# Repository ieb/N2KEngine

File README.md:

# N2K Engine Monitor

This monitors an engine, mostly temperatures and fuel, emitting suitable N2K messages. Targeting a Volvo Penta D2-40. Code and pcb are based on the interface board in https://github.com/ieb/EngineManagement, however this time the pcb is from scratch using a Atmel 328p directly to make the unit more robust. The original has been in service for 3 years with no problems seen, outlasting the Volvo Penta MDI unit, which failed 2x in < 4 years. Ok, the replacement was based on relays following the Perkins schematic for the same engine, so not really hard to do.

# PCB

Single board. If using a 328p chip you will need to flash the bootloader. See programBootLoader for details. 

## 328p based board 

<div>

</div>

## Attiny3226 Board, 12bit ADCs and better RPM accuracy

<div>

</div>

# Setup

Setup starting with a new board, this is for 3226 which the preferred board.

* Test the board supply to check power consumption, should be about 30mA at both 5v and 12v.
* Connect up a UDPI programmer, and serial monitor.
* Burn Fuses, and tune the internal clock on the 3226, see tuning3226/README.md
* Upload the code.
* Connect a CAN bus with 1 other device.
* Verify CAN messages are sent and received (menu item d)
* Measure and set the supply voltage to the chip after powering with 12v. (menu item V)
* Check the Sensor diagnostics (menu item D, and M), might need to connect some NTC sensors and fake up flywheel source.
* Set the engine hours to match the existing board.
* Install the board

## Connection notes

* The GND connection must be made to the engine block (star pattern) to avoid GND voltage differences when the anternator is charging. Do not GND on the battery as that will result in dips in the coolant temperature of 5C or more. The battery voltage will include the GND drop on the charging line.

* The exhaust NCT should be connected to a part of the wet exhaust with good thermal connection to the inside of the exhaust. Do not connect to the elbow on the engine as this could result in false alarms when starting a warm engine. The trigger level is 45C or an 8C every 30s rise. Typically an exaust in UK waters on a D2-40 rests at 34-37C and rises rapidly should raw water fail.

## Changes from original build 4 years ago

* All components SMD, no draughtboards or modules with pin headers to fail.
* Switched from a LM385 to a LMV393 for the flywheel pulse generator as all I need is a clean square wave to count the pulses. (actually I miss ordered 10 LMV393's and then switched over).
* Changed to a 16MHz crystal on the MCP2515 since this is what the 328p is using. Perhaps 1 crystal would work for both, but probably not.

# Memory usage

after reducing memory requirements (580 used before), varies up an down a bit with debug.

attiny3226

    RAM:   [==        ]  20.1% (used 619 bytes from 3072 bytes)
    Flash: [========  ]  81.1% (used 26579 bytes from 32768 bytes)
NB, no malloc in use in code.
Over 77% Flash usag pio inspect no longer works, however removing One wire code may give enough space for debug symbols to allow inspect to work

# Status bits.

The status bits in PGN 127489 are set to indicate an alarm condition.

Alarm set levels and alarm clear levels are in enginesensors.h

WHen an alarm condition is set if the check engine, maintenance or emergency stop bits are set, they are not
cleared when the alarm clears. Generally advisable to stop the engine and check.

Emergency stop will be set when temperatures are too high. Best to stop the engine before damage occurs.

Over Temperature status 1 bit 1 set when over temperature is suspected including coolant (> 97C), exhaust > 45C, alternator > 110C, engine room > 70C. Will also set check engine and engine emergency shutdown alarms.

Low oil pressure alarm is set when oil pressure is < 10psi.

If sensors fail then engine comms alarm is set.

Water flow alarm uses the wet exhaust silencer probe as a proxy for raw water flow. The probe is mounted on the silencer body, which is in direct contact with the wet exhaust but thermally isolated from the engine block and heat exchanger — so silencer temperature reflects exhaust gas vs raw water flow only, and is not biased by block temperature on a warm restart. Two independent triggers, both gated on engine running, past the start-up grace period, and not stopping:

* Absolute over-temp: exhaust > 45C. WATER_FLOW and CHECK_ENGINE are set on the first sample; EMERGENCY_STOP is held off until the condition has persisted for 5s so a single noisy ADC sample cannot trip it.
* Rate-of-rise: exhaust climbs more than 8C in any 30s window once past the 35C baseline. This catches a flow failure before the absolute threshold (the 21-Jun-2026 incident showed a +9C rise in the first 30s while still well below 45C).

A coolant-vs-exhaust convergence check was previously included but removed: on a warm restart the silencer takes several minutes to thermalize while coolant is already at operating temperature, producing a coolant–exhaust gap that approaches the trip margin under entirely healthy conditions.

The alarm clears only once exhaust drops below 38C (widened from 40C) to avoid chatter on a cooling elbow.

Charge indicator alarm is set when the alternator voltage is < 12.8V

Engine shutdown alarm will be set when the engine is shutting down.

Other alarms are not set at this time.

# Building and Uploading

## Attiny3226 based board

Use UDPI. I use the old, slow and slightly buggy jtag2udpi programmer loaded onto an Uno. I use https://github.com/ieb/jtag2updi forked just in case. After programming the Uno needs a 10uF cap between reset and ground to prevent a reset on the Uno when programming starts.  The UDPI output is on Digital Pin 6 and connects via a 4K7 Resistor to the UDPI pin on the Attiny3226. The target board should be powered separately, and the serial monitor can remain attached while programming. Do not power the board using both a serial converter and the 12v power supply as this will cause the serial port to draw too much USB current and be shutdown. Programing setup is in platformio.ini. Before programming a fresh chip, set the fuses to set the CPU Frequency.

Fresh boards also need to go through a runing process , see tuning3226/

Obviously edit platform.ini with the correct serial ports for upload and monitoring.

    pio run -e attiny3226 -t fuses

Then upload code with an upload command. Fuses only need to be set once per chip.

    pio run -e attiny3226 -t upload

To monitor 

    pio device monitor

### Clock Tuning 3226

The 3226 board uses an internal oscilator due to lack of pins and so it needs tuning from a board with a quartz crystal as per https://github.com/SpenceKonde/megaTinyCore/blob/master/megaavr/extras/Ref_Tuning.md. The Tuning source needs to be https://github.com/SpenceKonde/megaTinyCore/tree/master/megaavr/libraries/megaTinyCore/examples/TuningSource uploaded onto a Uno or any 328p with pin 9 available. The UNO must have an real crystal not a resonator.  The tuning code is https://github.com/SpenceKonde/megaTinyCore/tree/master/megaavr/libraries/megaTinyCore/examples/megaTinyTuner, but for these boards must be modified to use PB1 as the timing pin since this is exposed directly. (Oil pressure sense).  Copies of both of these are in tuning as they needed minor modifications.

## 328p based board

Can be built on any 328p suitably wired, however to build using the pcb design first flash a bootloader, see [programBootLoader/README.md] for details, then come back here.

Having flashed with the urbootloader connect a serial adapter configured for 5V to the serial header pins, adjust platform.ini to reflect the serial port and run

    pio run -t upload

to monitor

    pio device monitor

Do not attempt to power the board both on the 12v line and through the serial port 5v at the same time. This will probably shutdown the USB port on your laptop (or worse produce some smoke) Monitoring over serial can be done provided only GND, TX and RX are attached. Ie no power from the serial adapter.

# LM393 RPM to pulses

Critical that this chip as a 100nF decoupling capacitor. Without it it will generate pulses from power supply noise with the inputs shorted together. See schematic. LTSpice models don't predict this behavior.

# Engine Events

Stores upto 29 events in EEPROM, with a 15s resolution and one of upto 255 types.
All the following PGNS have standard priorietary PGN format + a Function code byte.
The Manufactore code is 2046 and the Industry is Marine, ie 4.

# PGN Abuse

Since Raymarine instuments display only a asubset of PGNs, some are beeing abused to get critical temperatures avialable on the insturments.

* alternator temperature, critical for LiFePO4 charging, is sent as oil temperature in Dynamic Engine Parameters (PGN 127489)
* ehxhaust temperature, critical for raw water flow monitoring, is sent as transmission oil temperature in Dynamic Transmiossion Parameters (PGN 127493L)

# Temperature PGN 130312 non standard IDs

* Exhaust temperature is sent as ID 30
* Additional OneWire Temperature probes are sent as IDs 31-35 where present.

## PGN 65305L

Standard  Packet proprietary, 8 bytes

| Field | Length | Value     | Description            |
|-----------------------------------------------------|
| 1     | 11 bits| 2046      | Manufacturer code      |
| 2     | 2 bits |           | Rserved                |
| 3     | 3 bits | 4 (0b100) | Industry Code          |
| 4     | 8 bits |           | Requst Function Number |
| 5     | 5 bytes|           | reserved/payload       |

|  Function | Description         | Valid PGN | Response                              |
|-----------|---------------------|-----------|---------------------------------------|
| 11        | Get events          | 65305L    | Events PGN 130817L Functon 12         |
| 12        | Get events response | 130817L   | List of events                        |
| 13        | Clear events        | 65305L    | ACK PGN 65305L Functon 14, no payload |
| 14        | Clear events ACK    | 65305L    | Ack clear events, no payload          |

## PGN 130817L

| Field | Length | Value     | Description            |
|-------|--------|-----------|------------------------|
| 1     | 11 bits| 2046      | Manufacturer code      |
| 2     | 2 bits |           | Rserved                |
| 3     | 3 bits | 4 (0b100) | Industry Code          |
| 4     | 8 bits |           | Requst Function Number |

## Function 12

| Field   | Length  | Value               | Description                            | 
|---------|---------|---------------------|----------------------------------------|
| 4       | 1 byte  | uint8_t             | Number of events                       |
| 5+(n*4) | 1 byte  | uint8_t             | Event ID                               |
| 6+(n*4) | 3 bytes | 3Byte UDouble 0.001 | Engine Hours of event (15s resolution) |

| Event ID | Meaning |
|----------|---------|
| 0        | Current engine hours, no event |
| 1        | Engine Stop |
| 2        | Low Oil Pressure |
| 3        | High Coolant Temperature |
| 4        | High Exhaust Temperature |
| 5        | High Alternator Temperature |
| 6        | High Engine Room Temperature |

# Todo

* [x] build board.
* [x] Flash bootloader and test
* [x] Port code from original
* [x] Allow for 16MHz MCP2515 oscillator, current library uses 8MHz.
* [x] Handle when engine not running, now that device is powered from CanBus
* [x] Reduce memory requirements in EngineSensorts and bind measurements to messages.
* [x] PR SmallNMEA2000 with changes
* [x] Test and Calibrate NTCs
* [x] Test and Calibrate Coolant and fuel
* [x] Test On N2K Bus
* [x] Implement 1 wire
* [x] Allow Engine Hours to be set via serial
* [x] Improve status and diagnostics to include n2k traffic
* [x] Implement status alarms
* [x] Consider swapping NTC4 for a oil pressure sensor if it can be accommodated.
* [x] Power from Engine supply since oil pressure sensors use > 10mA typically. This means fuel levels and temperature will only be available with engine controls turned on.
* [x] Check voltage calibration, some doubt over digtal multi meter accuracy used previously - verified against a ADS1115 to be accurate
* [x] Add firmware version, shows on the help, press h when connected over serial.
* [x] Create a attiny3226 based board, with 12bit ADCs for better resolution on the voltages.
* [x] Calibrate CPU clock
* [x] Verify RPM accuracy (measured at +- 0.2% relative to calibrated 16Mhz crystal)
* [x] Verify NTC and other ADC readings.
* [x] Install onboard
* [x] Implement event storage
* [x] Implement PGN proprietary messages to query engine events.
* [x] Update schematic to improve ADC stability when charging main LiFePO4s
* [x] Fix OneWire on Attiny3226 (see lib/vportonewire)
* [x] Fix event streaming to contain the right number of events including current hours.
* [x] Read stop button, on PC0. This will go to 12V when the solenois is powered.
* [x] Lowered alternator low voltage alarm to 12.2v and added window for overheat to combat high noise levels on the coolant sensor.
* [x] Added window period for all alarms to avoid 1 reading triggering alarm condition, set a 5s. 
* [x] Fixed (hopefully, need to test on engine) noise in in Engine Coolant readings, due to 12v ripple.
* [ ] Check the divders, which we specked at 100K/47K which could be too large for the ADC capacitance.

# Could do... but probably will not

The board currently runs of switched engine power, so to read fuel tank and batteries the engine has to be turned on. This is good, since power consumption becomes irrelevant although its typically < 80mA. I could optimize so that the board could be powered from the Can bus, but probably wont. Better to have it off when 
not relevant.. eg when sailing.

# New Board check list

* Oil sensor with pot
* NTCs, set Vdd then 10K == 25C, 22K == 8C, Check thermstor against room temp and body temp.
* Check Fuel 190R == full 0R == empty, linear, 120R == 120/190 = 63%  47/190 == 24
* Check AltV by connecting to suppy V
* Check Coolant, Supply -> 1K top. 22R == 120C, 120R == 60+10*(134-120)/(134-97) = 63
* Check RPM with a 1KHz signal
* Check oneWire
* Check CAN and engine events are responding, verifies can read and write.

# Engine overheat data from 21 July 2026.

Had been motoring for about 45m, 2.2K rpm all stable.

* 10:08:45 Coolant 87C, Exhaust 38.4C, Engine Room 57. raw water hose detaches, sudden drop in Engine Room temperature due to water spraying engine bay. Exhaust note changed.
* 10:09:00 Coolant 90C, Exhaust 40.2, Engine 50C
* 10:09:15 Coolant 92.7C, Exhaust 47.1, Engine 49.4C
* 10:09:30 Coolant 95.2C, Exhaust 51.9, Engine 48.6C  <<< Should have alarmed here.
* 10:09:45 Coolant 97.4C, Exhaust 57.9, Engine 47.3C
* 10:09:55 Coolant 98.3C, Exhaust 62.6, Engine 47.1C  engine was turned off before overheat.

Exhaust elbow temperature rises rapidly 22C over 1m vs 8C over the same period for the engine coolant temperature, although at the time no raw water alarm sounded as the limit was set at 80C and there was no display showing exhaust temperature.

Exhaust elbow temperature seems to be a strong indicator of water flow once the engine is running at temperature.

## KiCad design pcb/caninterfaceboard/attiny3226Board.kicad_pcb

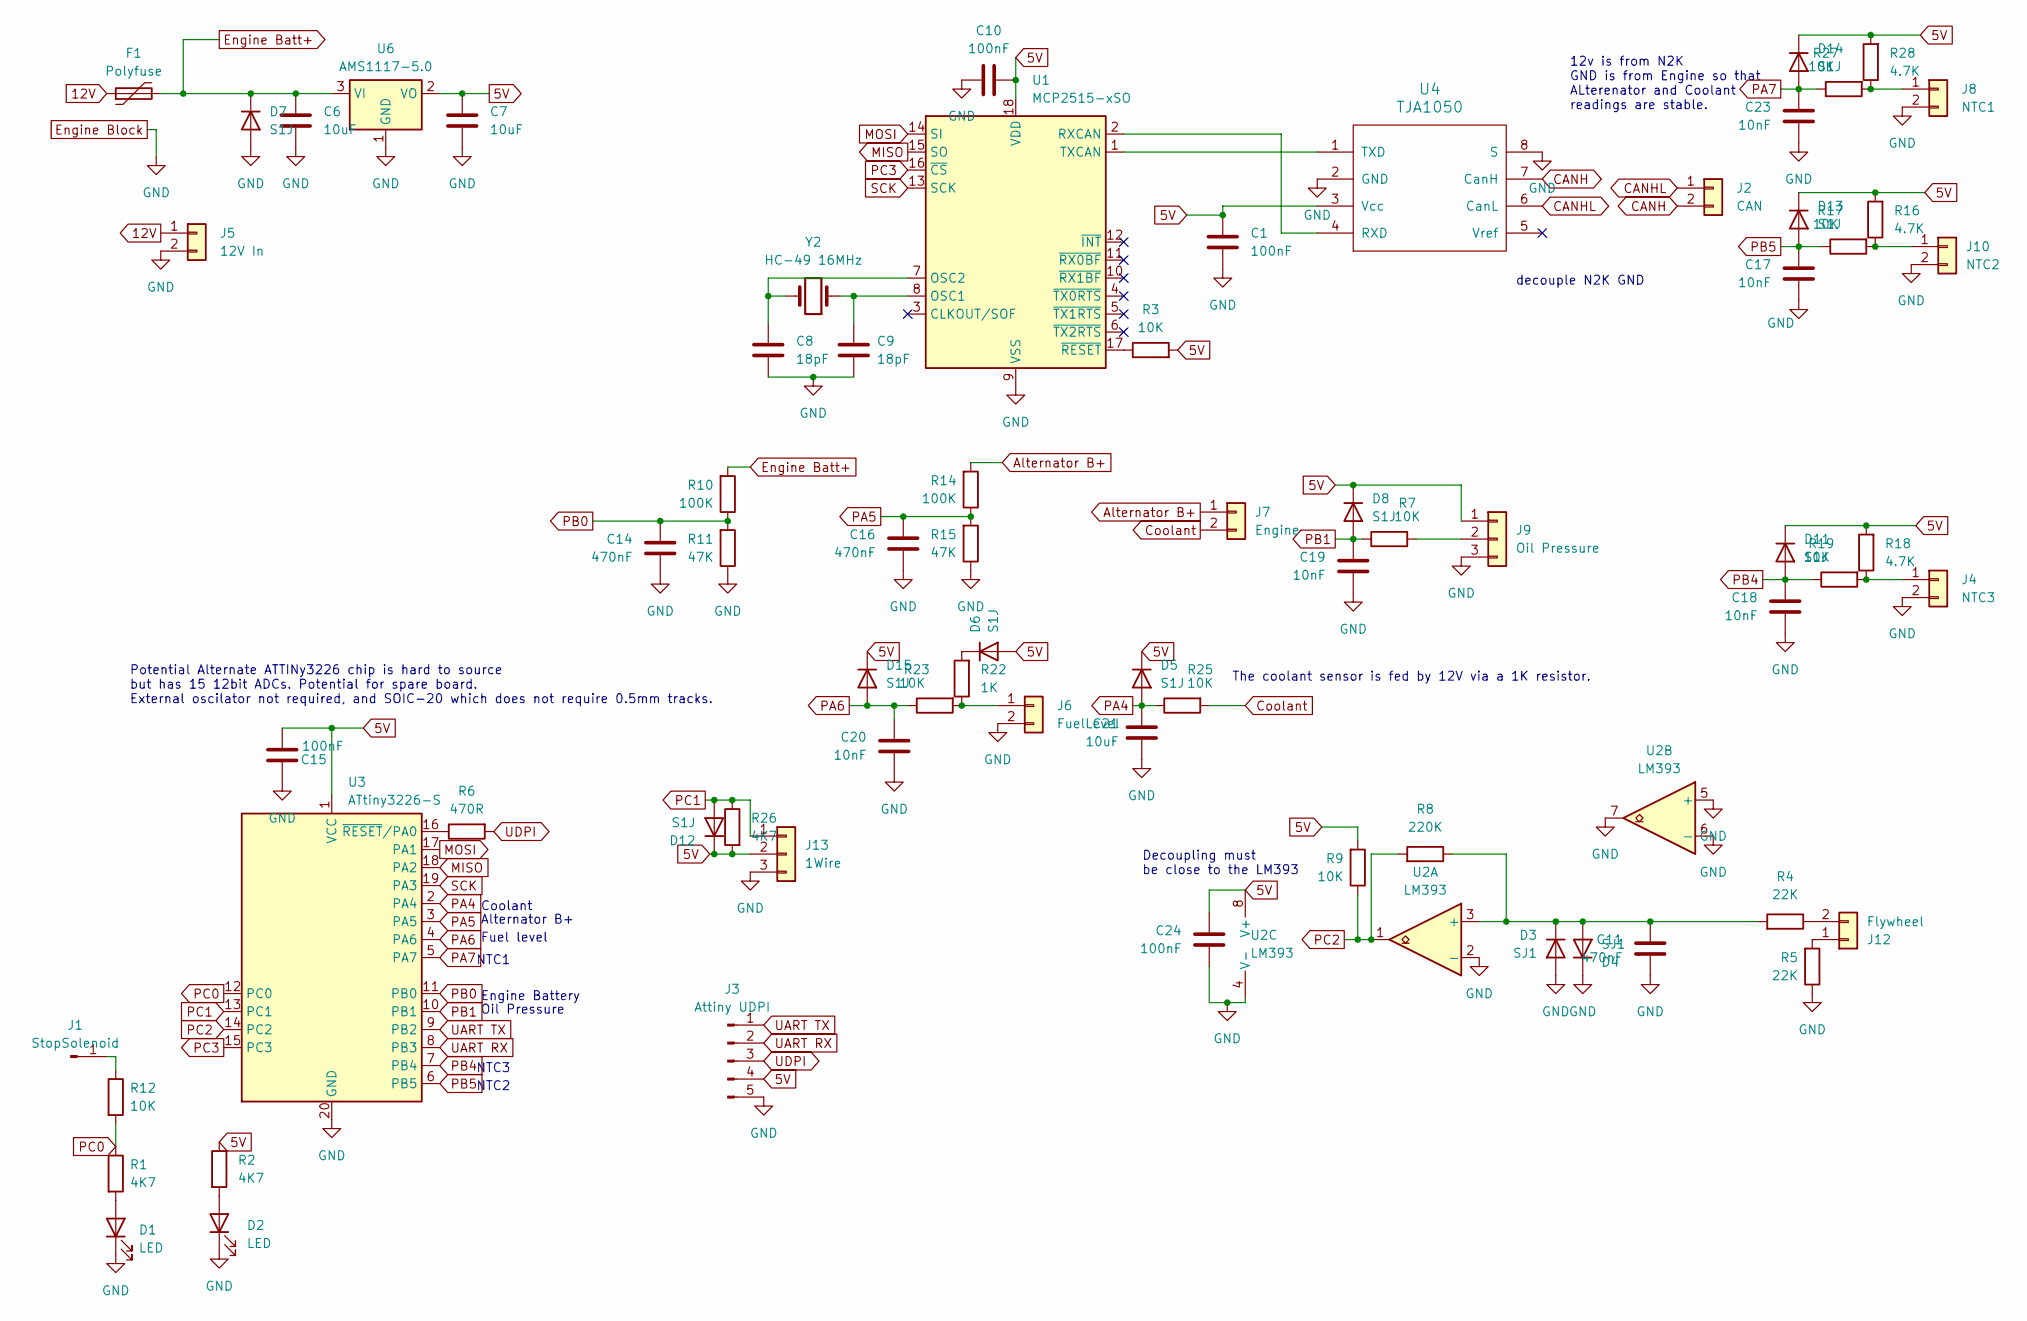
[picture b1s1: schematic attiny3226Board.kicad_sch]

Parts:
C1, C10, C15, C24: 100nF; C_0805_2012Metric_Pad1.18x1.45mm_HandSolder
C6, C7: 10uF; C_1206_3216Metric_Pad1.33x1.80mm_HandSolder
C8, C9: 18pF; C_0805_2012Metric_Pad1.18x1.45mm_HandSolder
C11, C14, C16: 470nF; C_0805_2012Metric_Pad1.18x1.45mm_HandSolder
C17, C18, C19, C20, C23: 10nF; C_0805_2012Metric_Pad1.18x1.45mm_HandSolder
C21: 10uF; C_0805_2012Metric_Pad1.18x1.45mm_HandSolder
D1, D2: LED; LED_0805_2012Metric_Pad1.15x1.40mm_HandSolder
D3, D4: SJ1; D_SOD-123
D5, D6, D7, D8, D11, D12, D13, D14, D15: S1J; D_0805_2012Metric_Pad1.15x1.40mm_HandSolder
F1: Polyfuse; Fuse_1812_4532Metric_Pad1.30x3.40mm_HandSolder
J1: StopSolenoid; PinSocket_1x01_P2.54mm_Vertical
J2: CAN; TerminalBlock_Phoenix_MKDS-1,5-2-5.08_1x02_P5.08mm_Horizont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
J3: Attiny UDPI; PinHeader_1x05_P2.54mm_Vertical
J4: NTC3; TerminalBlock_Phoenix_MKDS-1,5-2-5.08_1x02_P5.08mm_Horizont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
J5: 12V In; TerminalBlock_Phoenix_MKDS-1,5-2-5.08_1x02_P5.08mm_Horizont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
J6: FuelLevel; TerminalBlock_Phoenix_MKDS-1,5-2-5.08_1x02_P5.08mm_Horizont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
J7: Engine; TerminalBlock_Phoenix_MKDS-1,5-2-5.08_1x02_P5.08mm_Horizont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
J8: NTC1; TerminalBlock_Phoenix_MKDS-1,5-2-5.08_1x02_P5.08mm_Horizont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
J9: Oil Pressure; TerminalBlock_Phoenix_MKDS-1,5-3-5.08_1x03_P5.08mm_Horizont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
J10: NTC2; TerminalBlock_Phoenix_MKDS-1,5-2-5.08_1x02_P5.08mm_Horizont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
J12: Flywheel; TerminalBlock_Phoenix_MKDS-1,5-2-5.08_1x02_P5.08mm_Horizont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
J13: 1Wire; TerminalBlock_Phoenix_MKDS-1,5-3-5.08_1x03_P5.08mm_Horizont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
R1, R2, R26: 4K7; R_0805_2012Metric_Pad1.20x1.40mm_HandSolder
R3, R7, R9, R12, R17, R19, R23, R25, R27: 10K; R_0805_2012Metric_Pad1.20x1.40mm_HandSolder
R4, R5: 22K; R_0805_2012Metric_Pad1.20x1.40mm_HandSolder
R6: 470R; R_0805_2012Metric_Pad1.20x1.40mm_HandSolder
R8: 220K; R_0805_2012Metric_Pad1.20x1.40mm_HandSolder
R10, R14: 100K; R_0805_2012Metric_Pad1.20x1.40mm_HandSolder
R11, R15: 47K; R_0805_2012Metric_Pad1.20x1.40mm_HandSolder
R16, R18, R28: 4.7K; R_0805_2012Metric_Pad1.20x1.40mm_HandSolder
R22: 1K; R_0805_2012Metric_Pad1.20x1.40mm_HandSolder
U1: MCP2515-xSO; SOIC-18W_7.5x11.6mm_P1.27mm
U2: LM393; SOIC-8_3.9x4.9mm_P1.27mm
U3: ATtiny3226-S; SOIC-20W_7.5x12.8mm_P1.27mm
U4: TJA1050; SOIC-8_3.9x4.9mm_P1.27mm
U6: AMS1117-5.0; SOT-223-3_TabPin2
Y2: HC-49 16MHz; Crystal_SMD_HC49-SD

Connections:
5V: C1.1, C7.1, C10.2, C15.2, C24.2, D5.1 (K), D6.2 (A), D8.1 (K), D11.1 (K), D12.1 (K), D13.1 (K), D14.1 (K), D15.1 (K), J3.4, J9.1, J13.2, R2.1, R3.2, R9.2, R16.2, R18.2, R26.2, R28.2, U1.18 (VDD), U2.8 (V+), U3.1 (VCC), U4.3 (Vcc), U6.2 (VO)
12V: F1.1, J5.1
Alternator B+: J7.1, R14.2
CANH: J2.2, U4.7 (CanH)
CANHL: J2.1, U4.6 (CanL)
Coolant: J7.2, R25.2
Engine Batt+: C6.1, D7.1 (K), F1.2, R10.2, U6.3 (VI)
Engine Block: C1.2, C6.2, C7.2, C8.1, C9.1, C10.1, C11.1, C14.1, C15.1, C16.1, C17.1, C18.1, C19.1, C20.1, C21.1, C23.1, C24.1, D1.1 (K), D2.1 (K), D3.2 (A), D4.1 (K), D7.2 (A), J3.5, J4.2, J5.2, J6.2, J8.2, J9.3, J10.2, J13.3, R5.1, R11.1, R15.1, U1.9 (VSS), U2.2 (-), U2.4 (V-), U2.5 (+), U2.6 (-), U2.7, U3.20 (GND), U4.2 (GND), U4.8 (S), U6.1 (GND)
MISO: U1.15 (SO), U3.18 (PA2)
MOSI: U1.14 (SI), U3.17 (PA1)
unnamed: D1.2 (A), R1.2
unnamed: D2.2 (A), R2.2
unnamed: C11.2, D3.1 (K), D4.2 (A), R4.2, R8.1, U2.3 (+)
unnamed: D6.1 (K), R22.2
unnamed: J1.1, R12.1
unnamed: J4.1, R18.1, R19.2
unnamed: J6.1, R22.1, R23.2
unnamed: J8.1, R27.2, R28.1
unnamed: J9.2, R7.2
unnamed: J10.1, R16.1, R17.2
unnamed: J12.1, R5.2
unnamed: J12.2, R4.1
unnamed: C9.2, U1.8 (OSC1), Y2.1
unnamed: C8.2, U1.7 (OSC2), Y2.2
unnamed: U1.2 (RXCAN), U4.4 (RXD)
unnamed: U1.1 (TXCAN), U4.1 (TXD)
unnamed: R3.1, U1.17 (~RESET)
unnamed: R6.1, U3.16 (~RESET/PA0)
PA4: C21.2, D5.2 (A), R25.1, U3.2 (PA4)
PA5: C16.2, R14.1, R15.2, U3.3 (PA5)
PA6: C20.2, D15.2 (A), R23.1, U3.4 (PA6)
PA7: C23.2, D14.2 (A), R27.1, U3.5 (PA7)
PB0: C14.2, R10.1, R11.2, U3.11 (PB0)
PB1: C19.2, D8.2 (A), R7.1, U3.10 (PB1)
PB4: C18.2, D11.2 (A), R19.1, U3.7 (PB4)
PB5: C17.2, D13.2 (A), R17.1, U3.6 (PB5)
PC0: R1.1, R12.2, U3.12 (PC0)
PC1: D12.2 (A), J13.1, R26.1, U3.13 (PC1)
PC2: R8.2, R9.1, U2.1, U3.14 (PC2)
PC3: U1.16 (~CS), U3.15 (PC3)
SCK: U1.13 (SCK), U3.19 (PA3)
UART RX: J3.2, U3.8 (PB3)
UART TX: J3.1, U3.9 (PB2)
UDPI: J3.3, R6.2

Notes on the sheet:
Alternator B+
Oil Pressure
NTC2
NTC1
12v is from N2K GND is from Engine so that ALterenator and Coolant readings are stable.
Coolant
The coolant sensor is fed by 12V via a 1K resistor.
Fuel level
Engine Battery
decouple N2K GND
Potential Alternate ATTINy3226 chip is hard to source but has 15 12bit ADCs. Potential for spare board. External oscilator not required, and SOIC-20 which does not require 0.5mm tracks.
NTC3
Decoupling must be close to the LM393

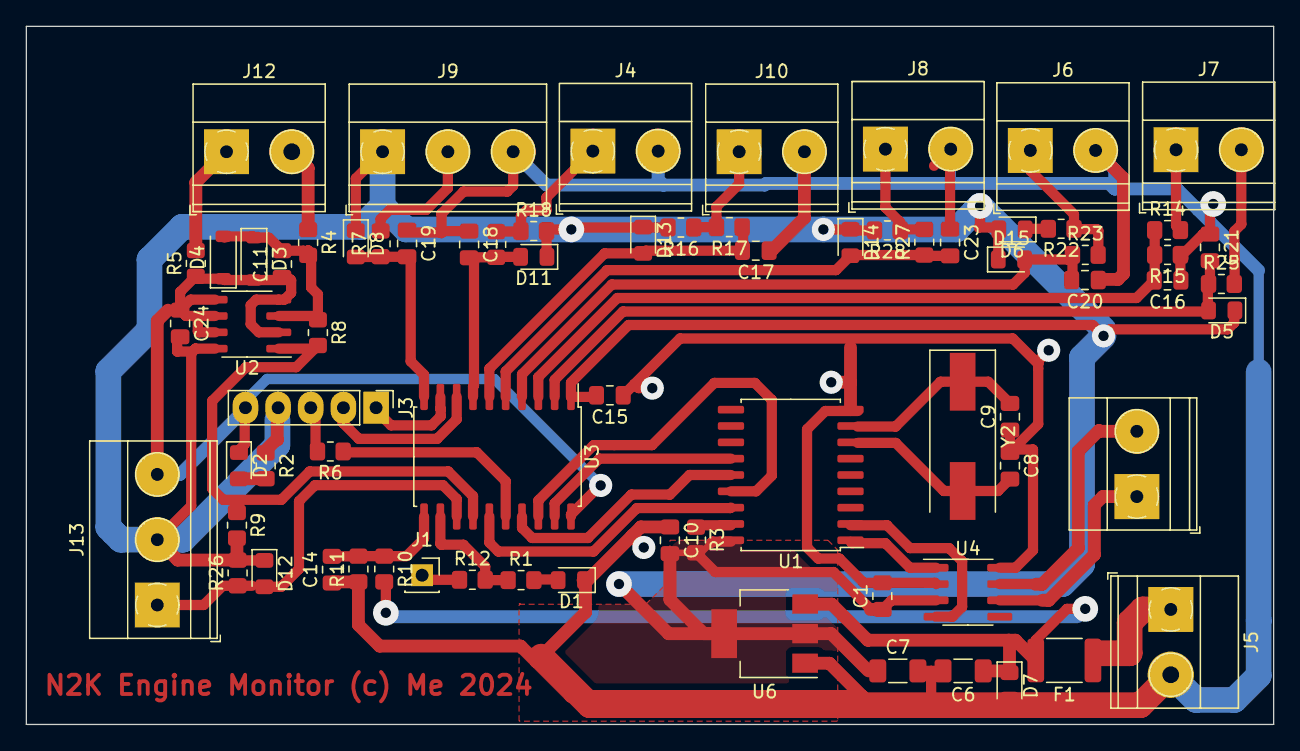
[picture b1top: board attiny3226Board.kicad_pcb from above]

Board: 2 copper layers, 97.0 x 54.3 mm, 73 parts (0 on the bottom side), 44 nets.

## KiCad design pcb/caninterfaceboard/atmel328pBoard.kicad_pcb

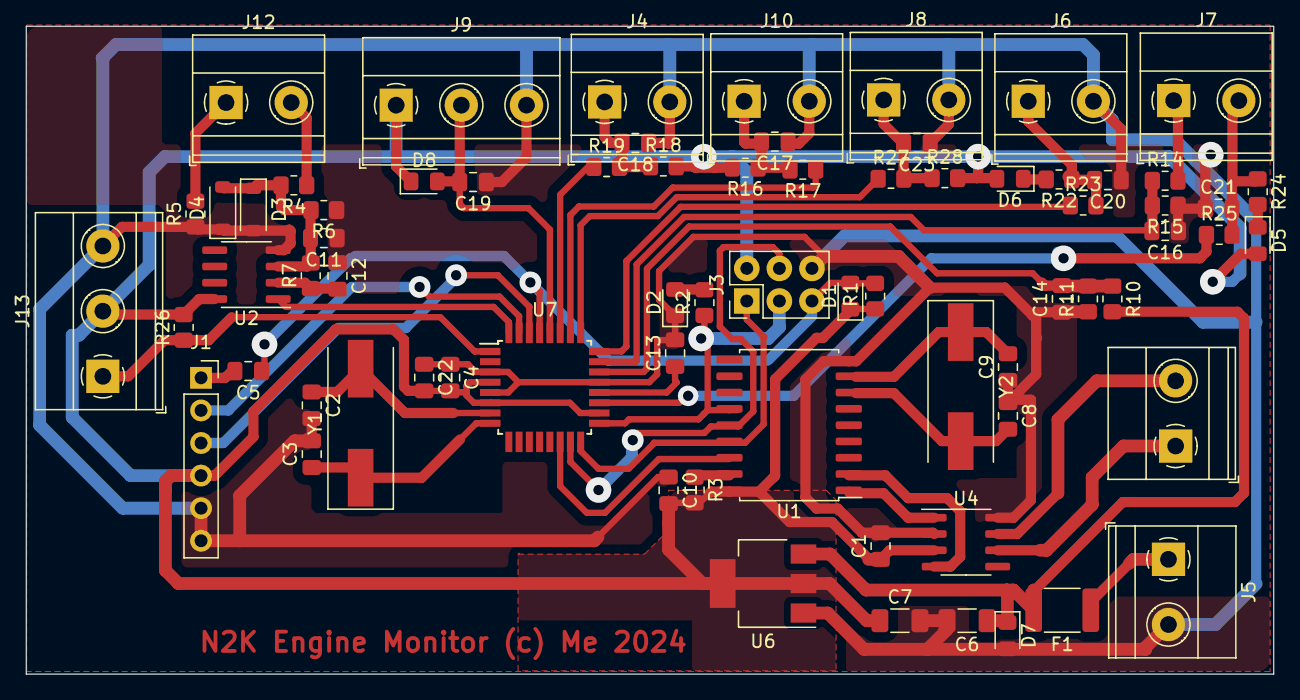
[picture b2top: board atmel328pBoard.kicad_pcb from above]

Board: 2 copper layers, 97.2 x 50.5 mm, 72 parts (0 on the bottom side), 45 nets.

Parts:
C1, C4, C5, C10, C13, C22: 100nF; C_0805_2012Metric_Pad1.18x1.45mm_HandSolder
C2, C3, C8, C9: 18pF; C_0805_2012Metric_Pad1.18x1.45mm_HandSolder
C6, C7: 10uF; C_1206_3216Metric_Pad1.33x1.80mm_HandSolder
C11, C12: 1uF; C_0805_2012Metric_Pad1.18x1.45mm_HandSolder
C14, C16: 1nF; C_0805_2012Metric_Pad1.18x1.45mm_HandSolder
C17, C18, C19, C20, C21, C23: 10nF; C_0805_2012Metric_Pad1.18x1.45mm_HandSolder
D1, D5, D6, D7, D8: S1J; D_0805_2012Metric_Pad1.15x1.40mm_HandSolder
D2: LED; LED_0805_2012Metric_Pad1.15x1.40mm_HandSolder
D3, D4: 1N5819; D_SOD-123
F1: Polyfuse; Fuse_1812_4532Metric_Pad1.30x3.40mm_HandSolder
J1: UART; PinSocket_1x06_P2.54mm_Vertical
J2: CAN; TerminalBlock_Phoenix_MKDS-1,5-2-5.08_1x02_P5.08mm_Horizont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
J3: AVR ISP; PinHeader_2x03_P2.54mm_Vertical
J4: NTC3; TerminalBlock_Phoenix_MKDS-1,5-2-5.08_1x02_P5.08mm_Horizont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
J5: 12V In; TerminalBlock_Phoenix_MKDS-1,5-2-5.08_1x02_P5.08mm_Horizont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
J6: FuelLevel; TerminalBlock_Phoenix_MKDS-1,5-2-5.08_1x02_P5.08mm_Horizont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
J7: Engine; TerminalBlock_Phoenix_MKDS-1,5-2-5.08_1x02_P5.08mm_Horizont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
J8: NTC1; TerminalBlock_Phoenix_MKDS-1,5-2-5.08_1x02_P5.08mm_Horizont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
J9: Oil Pressure; TerminalBlock_Phoenix_MKDS-1,5-3-5.08_1x03_P5.08mm_Horizont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
J10: NTC2; TerminalBlock_Phoenix_MKDS-1,5-2-5.08_1x02_P5.08mm_Horizont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
J12: Flywheel; TerminalBlock_Phoenix_MKDS-1,5-2-5.08_1x02_P5.08mm_Horizont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
J13: 1Wire; TerminalBlock_Phoenix_MKDS-1,5-3-5.08_1x03_P5.08mm_Horizont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
R1, R3: 10K; R_0805_2012Metric_Pad1.20x1.40mm_HandSolder
R2: 330R; R_0805_2012Metric_Pad1.20x1.40mm_HandSolder
R4, R5: 22K; R_0805_2012Metric_Pad1.20x1.40mm_HandSolder
R6, R22, R24: 1K; R_0805_2012Metric_Pad1.20x1.40mm_HandSolder
R7, R17, R19, R23, R25, R27: 100K; R_0805_2012Metric_Pad1.20x1.40mm_HandSolder
R10, R14: 1M; R_0805_2012Metric_Pad1.20x1.40mm_HandSolder
R11, R15: 470K; R_0805_2012Metric_Pad1.20x1.40mm_HandSolder
R16, R18, R28: 4.7K; R_0805_2012Metric_Pad1.20x1.40mm_HandSolder
R26: 4K7; R_0805_2012Metric_Pad1.20x1.40mm_HandSolder
U1: MCP2515-xSO; SOIC-18W_7.5x11.6mm_P1.27mm
U2: LM393; SOIC-8_3.9x4.9mm_P1.27mm
U4: TJA1050; SOIC-8_3.9x4.9mm_P1.27mm
U6: AMS1117-5.0; SOT-223-3_TabPin2
U7: ATmega328P-A; TQFP-32_7x7mm_P0.8mm
Y1, Y2: HC-49 16MHz; Crystal_SMD_HC49-SD

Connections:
5V: C1.1, C4.2, C7.1, C10.2, C22.2, D1.1 (K), D5.2 (A), D6.2 (A), D8.1 (K), J1.4, J3.2, J9.1, J13.2, R1.1, R3.2, R16.2, R18.2, R26.2, R28.2, U1.18 (VDD), U2.8 (V+), U4.3 (Vcc), U6.2 (VO), U7.4 (VCC), U7.6 (VCC), U7.18 (AVCC)
12V: F1.1, J5.1
A0: C16.2, R14.1, R15.2, U7.23 (PC0)
A1: R23.1, U7.24 (PC1)
A2: R27.1, U7.25 (PC2)
A3: R17.1, U7.26 (PC3)
A4: R19.1, U7.27 (PC4)
A5: C19.2, D8.2 (A), J9.2, U7.28 (PC5)
A6: R25.1, U7.19 (ADC6)
A7: C14.2, R10.1, R11.2, U7.22 (ADC7)
Alternator B+: J7.1, R14.2
CANH: J2.2, U4.7 (CanH)
CANHL: J2.1, U4.6 (CanL)
Coolant: C21.2, J7.2, R24.1, R25.2
D2: U2.1, U7.32 (PD2)
D3: J13.1, R26.1, U7.1 (PD3)
D10: U1.16 (~CS), U7.14 (PB2)
Engine Batt+: C6.1, D7.1 (K), F1.2, R10.2, U6.3 (VI)
Engine Block: C1.2, C2.2, C3.2, C4.1, C6.2, C7.2, C8.1, C9.1, C10.1, C11.1, C12.1, C13.2, C14.1, C16.1, C17.1, C18.1, C19.1, C20.1, C21.1, C22.1, C23.1, D2.1 (K), D3.2 (A), D4.1 (K), D7.2 (A), J1.5, J1.6, J3.6, J4.2, J5.2, J6.2, J8.2, J9.3, J10.2, J13.3, R5.1, R6.1, R11.1, R15.1, U1.9 (VSS), U2.4 (V-), U4.2 (GND), U4.8 (S), U6.1 (GND), U7.3 (GND), U7.5 (GND), U7.21 (GND)
ISP RST: C5.1, D1.2 (A), J3.5, R1.2, U7.29 (~RESET/PC6)
MISO: J3.1, U1.15 (SO), U7.16 (PB4)
MOSI: J3.4, U1.14 (SI), U7.15 (PB3)
unnamed: D2.2 (A), R2.2
unnamed: C11.2, D3.1 (K), D4.2 (A), R4.2, R6.2, R7.2, U2.3 (+)
unnamed: D5.1 (K), R24.2
unnamed: D6.1 (K), R22.2
unnamed: C18.2, J4.1, R18.1, R19.2
unnamed: C20.2, J6.1, R22.1, R23.2
unnamed: C23.2, J8.1, R27.2, R28.1
unnamed: C17.2, J10.1, R16.1, R17.2
unnamed: J12.1, R5.2
unnamed: J12.2, R4.1
unnamed: C9.2, U1.8 (OSC1), Y2.1
unnamed: C8.2, U1.7 (OSC2), Y2.2
unnamed: U1.2 (RXCAN), U4.4 (RXD)
unnamed: U1.1 (TXCAN), U4.1 (TXD)
unnamed: R3.1, U1.17 (~RESET)
unnamed: C12.2, R7.1, U2.2 (-)
unnamed: C13.1, U7.20 (AREF)
SCK: J3.3, R2.1, U1.13 (SCK), U7.17 (PB5)
UART DTR: C5.2, J1.1
UART RX: J1.2, U7.31 (PD1)
UART TX: J1.3, U7.30 (PD0)
XTAL1: C2.1, U7.7 (XTAL1/PB6), Y1.2
XTAL2: C3.1, U7.8 (XTAL2/PB7), Y1.1

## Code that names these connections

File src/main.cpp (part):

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
#ifdef __AVR_TINY_2__

#define ADC_ALTERNATOR_VOLTAGE PIN_PA5
#define ADC_FUEL_SENSOR PIN_PA6
#define ADC_EXHAUST_NTC1 PIN_PA7 // NTC1
#define ADC_ALTERNATOR_NTC2 PIN_PB5 // NTC2
#define ADC_ENGINEROOM_NTC3 PIN_PB4
#define ADC_OIL_SENSOR PIN_PB1
#define ADC_COOLANT_TEMPERATURE PIN_PA4
#define ADC_ENGINEBATTERY PIN_PB0


#define PIN_FLYWHEEL PIN_PC2
#define PIN_ONE_WIRE ONE_WIRE_PIN 

#define SNMEA_SPI_M0SI PIN_PA1 // Default pin
#define SNMEA_SPI_MISO PIN_PA2 // Default Pin
#define SNMEA_SPI_SCK  PIN_PA3 // Default pin
#define SNMEA_SPI_CS_PIN  PIN_PC3 // not default, set in constructor
#define LED_PIN PIN_PC0

#else

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
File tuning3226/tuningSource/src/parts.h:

#ifndef  PARTS_H_
// *INDENT-OFF*
// The indentation that it demands is stupid and wrong.
  #define  PARTS_H_
  #include <avr/io.h>
  #if   (defined(__AVR_ATmega16__)    || defined(__AVR_ATmega32__)    || defined(__AVR_ATmega64__)    ||  defined(__AVR_ATmega128__)   || \
         defined(__AVR_ATmega164A__)  || defined(__AVR_ATmega164PA__) || \
         defined(__AVR_ATmega324A__)  || defined(__AVR_ATmega324PA__) || defined(__AVR_ATmega324PB__) || defined(__AVR_ATmega644A__)  || \
         defined(__AVR_ATmega644PA__) || defined(__AVR_ATmega1284__)  || defined(__AVR_ATmega1284P__))
    #define __AVR_ATmega_Mighty__
    #ifndef TIMER0_TYPICAL
      #define TIMER0_TYPICAL              (1)
      /* Yes, timer0 is 8-bit timer with or without PWM */
      #define PIN_TIMER_OC0A              (PIN_PD5)
      #define PIN_TIMER_OC0B              (PIN_PD6)
      #define PIN_TIMER_T0                (PIN_PD4)

      #define TIMER1_TYPICAL              (1)
      /* Yes, timer1 is 16-bit PWM timer */
      #define PIN_TIMER_ICP1              (PIN_PB0)
      #define PIN_TIMER_OC1A              (9)
      #define PIN_TIMER_OC1B              (10)
      #define PIN_TIMER_T1                (PIN_PD5)

      #define TIMER2_TYPICAL              (1)
      /* Yes, timer2 is 8-bit async timer */
      #define PIN_TIMER_OC2A              (PIN_PD3)
      #define PIN_TIMER_OC2B              (PIN_PB3)
    #endif
  #elif  (defined(__AVR_ATmega641__) || defined(__AVR_ATmega1281__) || defined(__AVR_ATmega2561__) || \
          defined(__AVR_ATmega640__) || defined(__AVR_ATmega1280__) || defined(__AVR_ATmega2560__))
    #define __AVR_ATmega_Mega__
    #ifndef TIMER0_TYPICAL
      #define TIMER0_TYPICAL              (1)
      /* Yes, timer0 is 8-bit timer with or without PWM */
      #define PIN_TIMER_OC0A              (PIN_PD5)
      #define PIN_TIMER_OC0B              (PIN_PD6)
      #define PIN_TIMER_T0                (PIN_PD4)

      #define TIMER1_TYPICAL              (1)
      /* Yes, timer1 is 16-bit PWM timer */
      #define PIN_TIMER_ICP1              (PIN_PB0)
      #define PIN_TIMER_OC1A              (9)
      #define PIN_TIMER_OC1B              (10)
      #define PIN_TIMER_T1                (PIN_PD5)

      #define TIMER2_TYPICAL              (1)
      /* Yes, timer2 is 8-bit async timer */
      #define PIN_TIMER_OC2A              (PIN_PD3)
      #define PIN_TIMER_OC2B              (PIN_PB3)
      #define CONFIG_OK
    #endif
  #elif (defined(__AVR_ATtiny167__) || defined(__AVR_ATtiny87__))
    #define TINY_X7_TIMER
    #undef TIMER1_TYPICAL
    #undef TIMER0_TYPICAL
    #define TIMER0_TYPICAL  (0)
    #define TIMER1_TYPICAL  (87)
    #define PIN_TIMER_OC0A  (PIN_PA2)
    #define PIN_TIMER_OC1B  (PIN_PB1)
    #define CONFIGURE_PWM() (TCCR1D = 0x1 << OC1BU;)

  #elif (defined(__AVR_ATmega328__) || defined(__AVR_ATmega328P__) || defined(__AVR_ATmega328PB__) || \
         defined(__AVR_ATmega168__) || defined(__AVR_ATmega168P__) || defined(__AVR_ATmega168PB__) || defined(__AVR_ATmega168A__)  || defined(__AVR_ATmega168PA__) || \
         defined(__AVR_ATmega88__)  || defined(__AVR_ATmega88P__)  || defined(__AVR_ATmega88PB__)  || \
         defined(__AVR_ATmega8__) || (defined(__ABR_ATtiny88__) && F_CPU==16000000) /* MHET Tiny88 */)
    #define __AVR_ATmega_Mini__
    #ifndef TIMER0_TYPICAL
      #define TIMER0_TYPICAL              (1)
      /* Yes, timer0 is 8-bit timer with or without PWM */
      #define PIN_TIMER_OC0A              (PIN_PD5)
      #define PIN_TIMER_OC0B              (PIN_PD6)
      #define PIN_TIMER_T0                (PIN_PD4)

      #define TIMER1_TYPICAL              (1)
      /* Yes, timer1 is 16-bit PWM timer */
      #define PIN_TIMER_ICP1              (PIN_PB0)
      #define PIN_TIMER_OC1A              (9)
      #define PIN_TIMER_OC1B              (10)
      #define PIN_TIMER_T1                (PIN_PD5)

      #define TIMER2_TYPICAL              (1)
      /* Yes, timer2 is 8-bit async timer */
      #define PIN_TIMER_OC2A              (PIN_PD3)
      #define PIN_TIMER_OC2B              (PIN_PB3)
    #endif
    #define CONFIG_OK
  // we can handle the others without mess like what is seen below.
  // *INDENT-OFF* //This didn't work here!
  #elif (defined(__AVR_ATmega808__) || defined(__AVR_ATmega1608__) || defined(__AVR_ATmega3208__) || defined(__AVR_ATmega4808__) || \
defined(__AVR_ATmega809__) || defined(__AVR_ATmega1609__) || defined(__AVR_ATmega3209__) || defined(__AVR_ATmega4809__) )
  #define __AVR_ATmega_Zero__
  #else
    #if (defined(MEGATINYCORE) || defined(DXCORE) || defined(ATTINYCORE))
// Well then what the heck is it?
      #if   (defined(__AVR_ATtiny3217__) || defined(__AVR_ATtiny1617__) || defined(__AVR_ATtiny1604__) || defined(__AVR_ATtiny1607__) || \
defined(__AVR_ATtiny3216__) || defined(__AVR_ATtiny1616__) || defined(__AVR_ATtiny1606__) || defined(__AVR_ATtiny1614__) || \
defined(__AVR_ATtiny817__)  || defined(__AVR_ATtiny807__)  || defined(__AVR_ATtiny816__)  || defined(__AVR_ATtiny806__)  || \
defined(__AVR_ATtiny814__)  || defined(__AVR_ATtiny804__)  || defined(__AVR_ATtiny417__)  || defined(__AVR_ATtiny807__)  || \
defined(__AVR_ATtiny416__)  || defined(__AVR_ATtiny406__)  || defined(__AVR_ATtiny414__)  || defined(__AVR_ATtiny404__)  || \
defined(__AVR_ATtiny214__)  || defined(__AVR_ATtiny204__)  || defined(__AVR_ATtiny412__)  || defined(__AVR_ATtiny402__)  || \
defined(__AVR_ATtiny212__)  || defined(__AVR_ATtiny202__)  )
      #define __AVR_ATtiny_Zero_One__
      #elif (defined(__AVR_ATtiny3227__) || defined(__AVR_ATtiny1627__) || defined(__AVR_ATtiny3224__) || defined(__AVR_ATtiny1624__) || \
defined(__AVR_ATtiny3226__) || defined(__AVR_ATtiny1626__) || defined(__AVR_ATtiny827__)  || defined(__AVR_ATtiny826__)  || \
defined(__AVR_ATtiny827__)  )
      #define __AVR_ATtiny_Two__
      #elif (defined(__AVR_AVR128DA28__) || defined(__AVR_AVR128DA32__) || defined(__AVR_AVR128DA48__) || defined(__AVR_AVR128DA64__) || \
defined(__AVR_AVR64DA28__)  || defined(__AVR_AVR64DA32__)  || defined(__AVR_AVR64DA48__)  || defined(__AVR_AVR64DA64__)  || \
defined(__AVR_AVR32DA28__)  || defined(__AVR_AV324DA32__)  || defined(__AVR_AVR32DA48__)  )
      #define __AVR_DA__
      #elif (defined(__AVR_AVR128DB28__) || defined(__AVR_AVR128DB32__) || defined(__AVR_AVR128DB48__) || defined(__AVR_AVR128DB64__) || \
defined(__AVR_AVR64DB28__)  || defined(__AVR_AVR64DB32__)  || defined(__AVR_AVR64DB48__)  || defined(__AVR_AVR64DB64__)  || \
defined(__AVR_AVR32DB28__)  || defined(__AVR_AV324DB32__)  || defined(__AVR_AVR32DB48__)  )
      #define __AVR_DB__
      #elif (defined(__AVR_AVR16DD28__)  || defined(__AVR_AVR16DD32__)  || defined(__AVR_AVR16DD20__)  || defined(__AVR_AVR16DD14__)  || \
defined(__AVR_AVR64DD28__)  || defined(__AVR_AVR6DDA32__)  || defined(__AVR_AVR64DD20__)  || defined(__AVR_AVR32DD14__)  || \
defined(__AVR_AVR32DD28__)  || defined(__AVR_AV32DDA32__)  || defined(__AVR_AVR32DD20__)  || defined(__AVR_AVR64DD14__)  )
      #define __AVR_DD__
      #elif (defined(__AVR_AVR16DU28__)  || defined(__AVR_AVR16DU32__)  || defined(__AVR_AVR16DU20__)  || defined(__AVR_AVR16DU14__)  || \
defined(__AVR_AVR64DU28__)  || defined(__AVR_AVR64DU32__)  || \
defined(__AVR_AVR32DU28__)  || defined(__AVR_AVR32DU32__)  || defined(__AVR_AVR32DU20__)  || defined(__AVR_AVR32DU14__)  )
      #define __AVR_DU__
      #elif (defined(__AVR_AVR64EA48__) || defined(__AVR_AVR32EA48__) || defined(__AVR_AVR16EA48__) || \
defined(__AVR_AVR64EA32__) || defined(__AVR_AVR32EA32__) || defined(__AVR_AVR16EA32__) || defined(__AVR_AVR8EA32__) || \
defined(__AVR_AVR64EA28__) || defined(__AVR_AVR32EA28__) || defined(__AVR_AVR16EA28__) || defined(__AVR_AVR8EA28__))
      #define __AVR_EA__
      #elif (defined(__AVR_AVR64EA48__) || defined(__AVR_AVR32EA48__) || defined(__AVR_AVR16EA48__) || \
defined(__AVR_AVR64EB32__) || defined(__AVR_AVR32EB32__) || defined(__AVR_AVR16EB32__) || defined(__AVR_AVR8EB32__) || \
defined(__AVR_AVR64EB28__) || defined(__AVR_AVR32EB28__) || defined(__AVR_AVR16EB28__) || defined(__AVR_AVR8EB28__) || \
defined(__AVR_AVR64EB20__) || defined(__AVR_AVR32EB20__) || defined(__AVR_AVR16EB20__) || defined(__AVR_AVR8EB20__) || \
defined(__AVR_AVR64EB14__) || defined(__AVR_AVR32EB14__) || defined(__AVR_AVR16EB14__) || defined(__AVR_AVR8EB14__))
      #define __AVR_EB__
      #else
        #error "Unknown or unsupported part"
      #endif
    #else // DXCore, megaTinyCore, ATTinyCore
      #if (CLOCK_SOURCE & 0x0F) != 1 && ((CLOCK_SOURCE & 0x0F) != 2)
        #error "This is a TIMING REFERENCE. Using the internal oscillator would defeat the whole point!"
      #endif
    #endif // for the what if it's not a classic mega
  #endif
  #ifndef CONFIG_OK
    #error "Part unknown, or known but unsupported."
  #endif
#endif

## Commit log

2024-12-01 Created board and loaded bootloader
2024-12-01 Needed a readme
2024-12-02 Ported code and adjusted to new pcb
2024-12-04 reading sensors on demand where possible
2024-12-08 Bench tested
2024-12-10 Added oil pressure and status, modified pcb
2024-12-17 Added screenshots and case
2024-12-20 Added firmware version bound to git sha1
2025-01-06 Added a attiny3226 veresion for better ADC accuracy
2025-01-11 Saving WIP for visibility
2025-01-11 Fixed counter
2025-01-11 Cleaned up examples and added better introduction docs
2025-01-11 Corrected output to latest version
2025-01-11 Bisected and Fixed.
    Detail. If EEPROM is witten to continuously it will mess with ISRs
    on a attiny and cause millis and micros to not be stable.
    But was introduced by refactoring the storage of engine hours.
    Now need to check that the 328p code is not in the same state on
    the device where it was flashed as that could break the EEPROM
    on the chip.
2025-01-19 Finally mare the RPM to pulse amp stable
2025-04-07 Improved flywheel detection circuit
2025-04-13 Added protection for ovre voltages on measurements
2025-05-11 Fixed startup and hopefully shutdown alarms
2025-05-26 fixed shutdown alarms, flashed to controller
2025-06-23 Added Event recording and proprietary PGNS to query
2025-06-24 Improvd ADC stability
2025-06-24 Tested event storage and listing on a 328p
2025-06-27 Added and tested on proMini engine event responses
2025-06-27 Added the current engine hours to PGN130817
2025-07-06 Fixed Onewire on Attiny3226
2025-07-08 Fixed n events and added read stop solenoid
2025-07-22 Fixed spurious alarms
2025-07-31 Added grace period and set low rpm to < 800
2026-06-22 Attempt to make the coolant temperature more stable
2026-06-23 Improved raw water failure reporting
2026-06-28 Exhaust temp sensor is mounted on the wet exhaust silencer body, not the elbow
2026-06-28 Improved voltage sampling
